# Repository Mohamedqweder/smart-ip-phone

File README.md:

# Smart IP Phone

Schaltplan und PCB-Design für ein WLAN-basiertes IP-Telefon.
Entwickelt mit KiCad auf Basis des ESP32-WROOM-32.

## Dateien
- `Arbeit.kicad_sch` → Schaltplan
- `arbeit fertig.kicad_pcb` → PCB Layout
- `README_SmartIPPhone.pdf` → Vollständige Dokumentation

## Design
- Mikrocontroller: ESP32-WROOM-32
- Konnektivität: WLAN 802.11 b/g/n (VoIP/SIP)
- Tool: KiCad

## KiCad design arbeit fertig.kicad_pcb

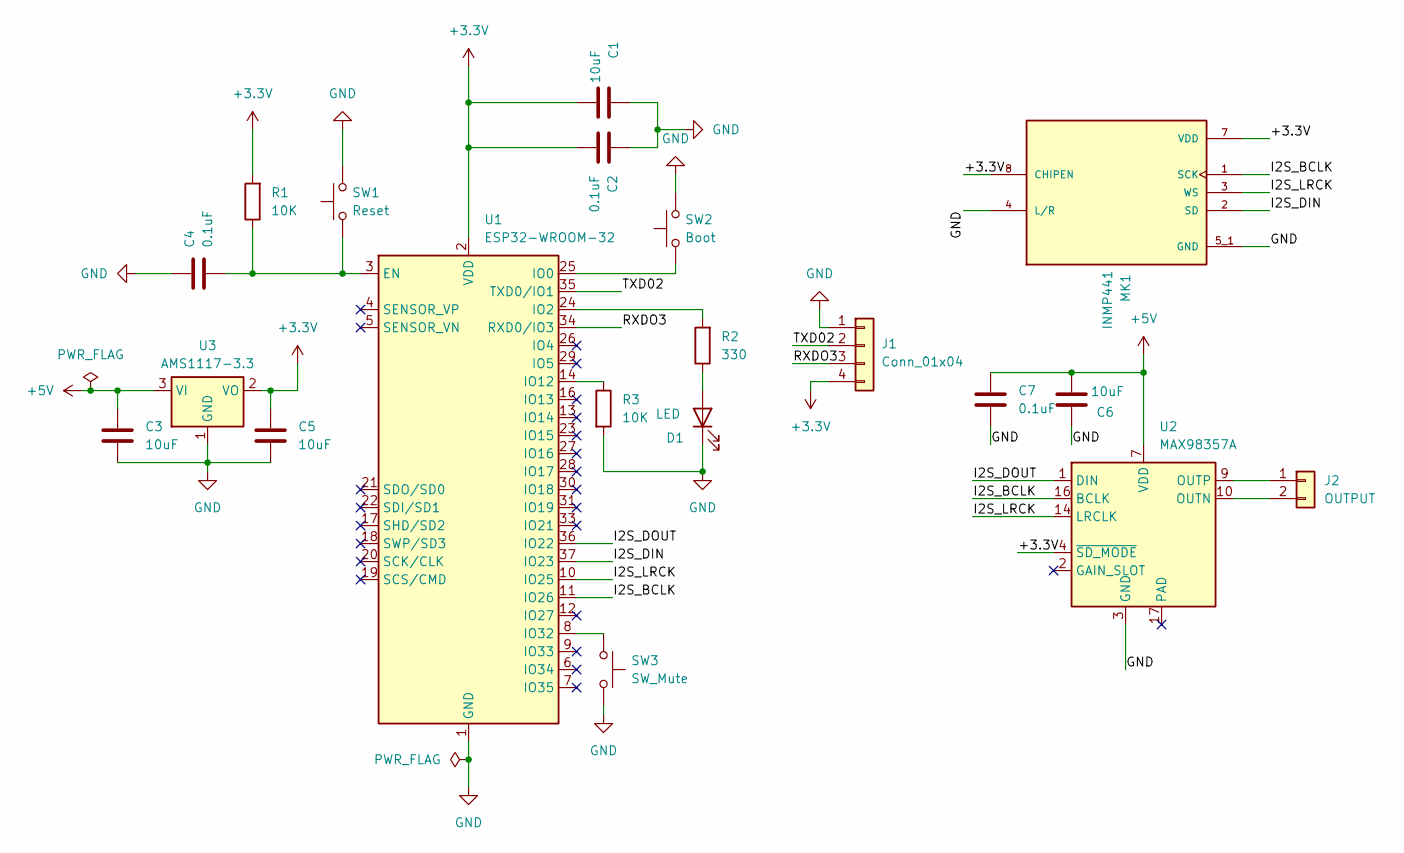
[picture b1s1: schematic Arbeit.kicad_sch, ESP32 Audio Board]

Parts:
C1, C3, C5, C6: 10uF; C_0603_1608Metric
C2, C4, C7: 0.1uF; C_0603_1608Metric
D1: LED; LED_0603_1608Metric
J1: Conn_01x04; PinHeader_1x04_P2.54mm_Vertical
J2: OUTPUT; PinHeader_1x02_P2.54mm_Vertical
MK1: INMP441; MIC_INMP441; PARTREV 1.1
R1, R3: 10K; R_0603_1608Metric
R2: 330; R_0603_1608Metric
SW1: Reset; SW_SPST_FSMSM
SW2: Boot; SW_SPST_FSMSM
SW3: SW_Mute; SW_SPST_FSMSM
U1: ESP32-WROOM-32
U2: MAX98357A; TQFN-16-1EP_3x3mm_P0.5mm_EP1.23x1.23mm
U3: AMS1117-3.3; SOT-223-3_TabPin2

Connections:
+3.3V: C1.2, C2.2, C5.1, J1.4, MK1.7 (VDD), MK1.8 (CHIPEN), R1.2, U1.2 (VDD), U2.4 (~SD_MODE), U3.2 (VO)
+5V: C3.1, C6.2, C7.1, U2.7 (VDD), U2.8 (VDD), U3.3 (VI)
/I2S_BCLK: MK1.1 (SCK), U1.11 (IO26), U2.16 (BCLK)
/I2S_DIN: MK1.2 (SD), U1.37 (IO23)
/I2S_DOUT: U1.36 (IO22), U2.1 (DIN)
/I2S_LRCK: MK1.3 (WS), U1.10 (IO25), U2.14 (LRCLK)
/RXDO3: J1.3, U1.34 (RXD0/IO3)
/TXD02: J1.2, U1.35 (TXD0/IO1)
GND: C1.1, C2.1, C3.2, C4.1, C5.2, C6.1, C7.2, D1.1 (K), J1.1, MK1.4 (L/R), MK1.5_1 (GND), MK1.5_2 (GND), MK1.6 (GND), MK1.9 (GND), R3.2, SW1.2, SW2.2, SW3.2, U1.1 (GND), U1.15 (GND), U1.38 (GND), U1.39 (GND), U2.3 (GND), U2.11 (GND), U2.15 (GND), U3.1 (GND)
unnamed: D1.2 (A), R2.1
unnamed: J2.1, U2.9 (OUTP)
unnamed: J2.2, U2.10 (OUTN)
unnamed: C4.2, R1.1, SW1.1, U1.3 (EN)
unnamed: SW2.1, U1.25 (IO0)
unnamed: R2.2, U1.24 (IO2)
unnamed: R3.1, U1.14 (IO12)
unnamed: SW3.1, U1.8 (IO32)

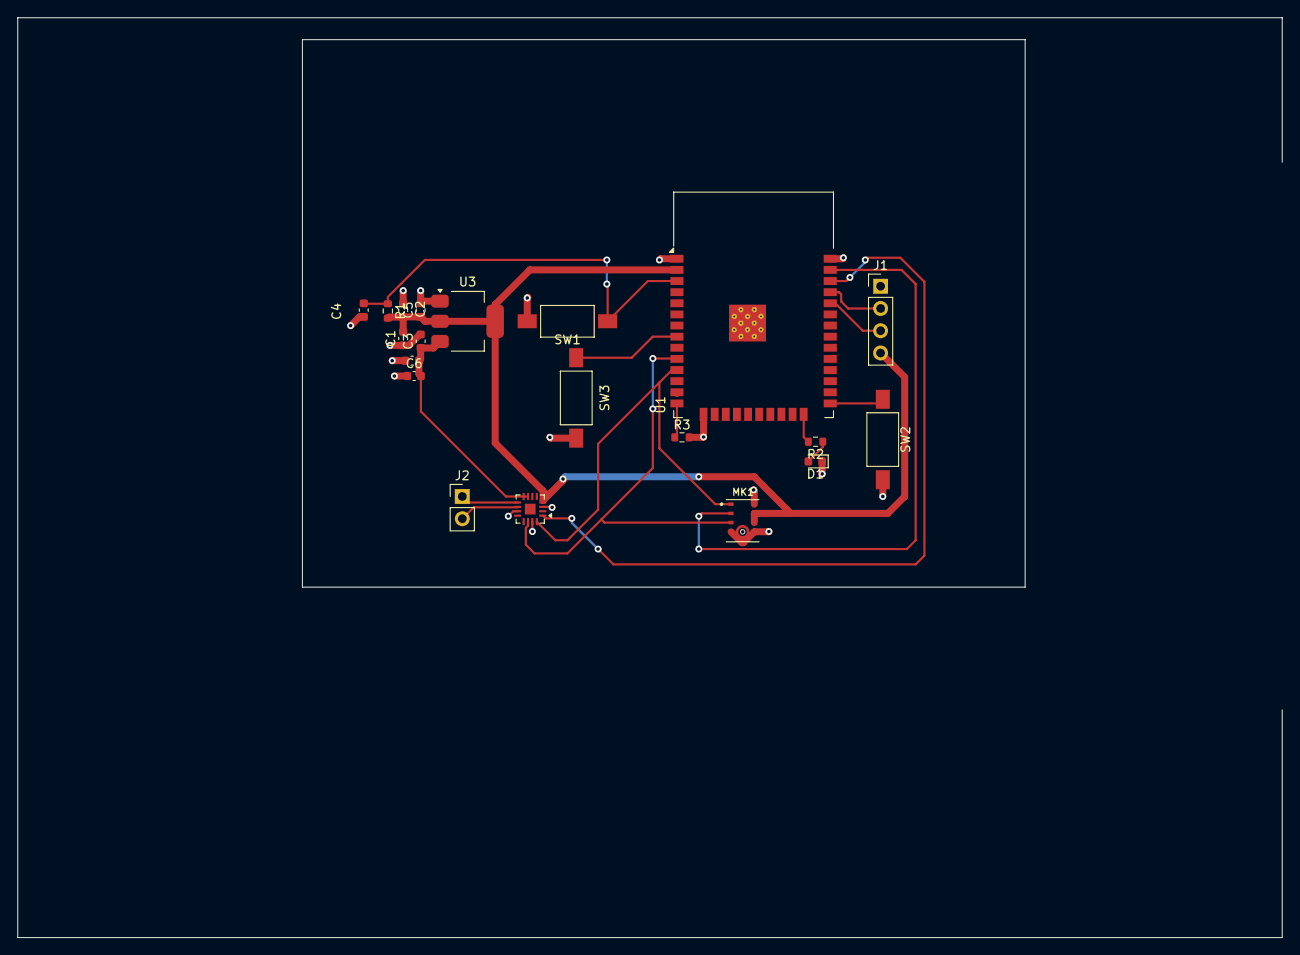
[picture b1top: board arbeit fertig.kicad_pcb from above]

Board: 2 copper layers, 144.3 x 105.0 mm, 20 parts (0 on the bottom side), 17 nets.

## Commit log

2026-05-17 README.md
